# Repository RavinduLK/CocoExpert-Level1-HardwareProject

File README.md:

# CocoExpert-Level1-HardwareProject
CocoExpert is an automated coconut breaking, scraping, and grinding machine with a focus on ensuring safety for housewives and frequent users, thereby eliminating the need for manual intervention

# Machine Animation Video
https://drive.google.com/drive/u/0/folders/18UEq-plaGjheWkudtf2PqrmO_yfCV39f

# Final Schematic Diagram

# Block Diagram

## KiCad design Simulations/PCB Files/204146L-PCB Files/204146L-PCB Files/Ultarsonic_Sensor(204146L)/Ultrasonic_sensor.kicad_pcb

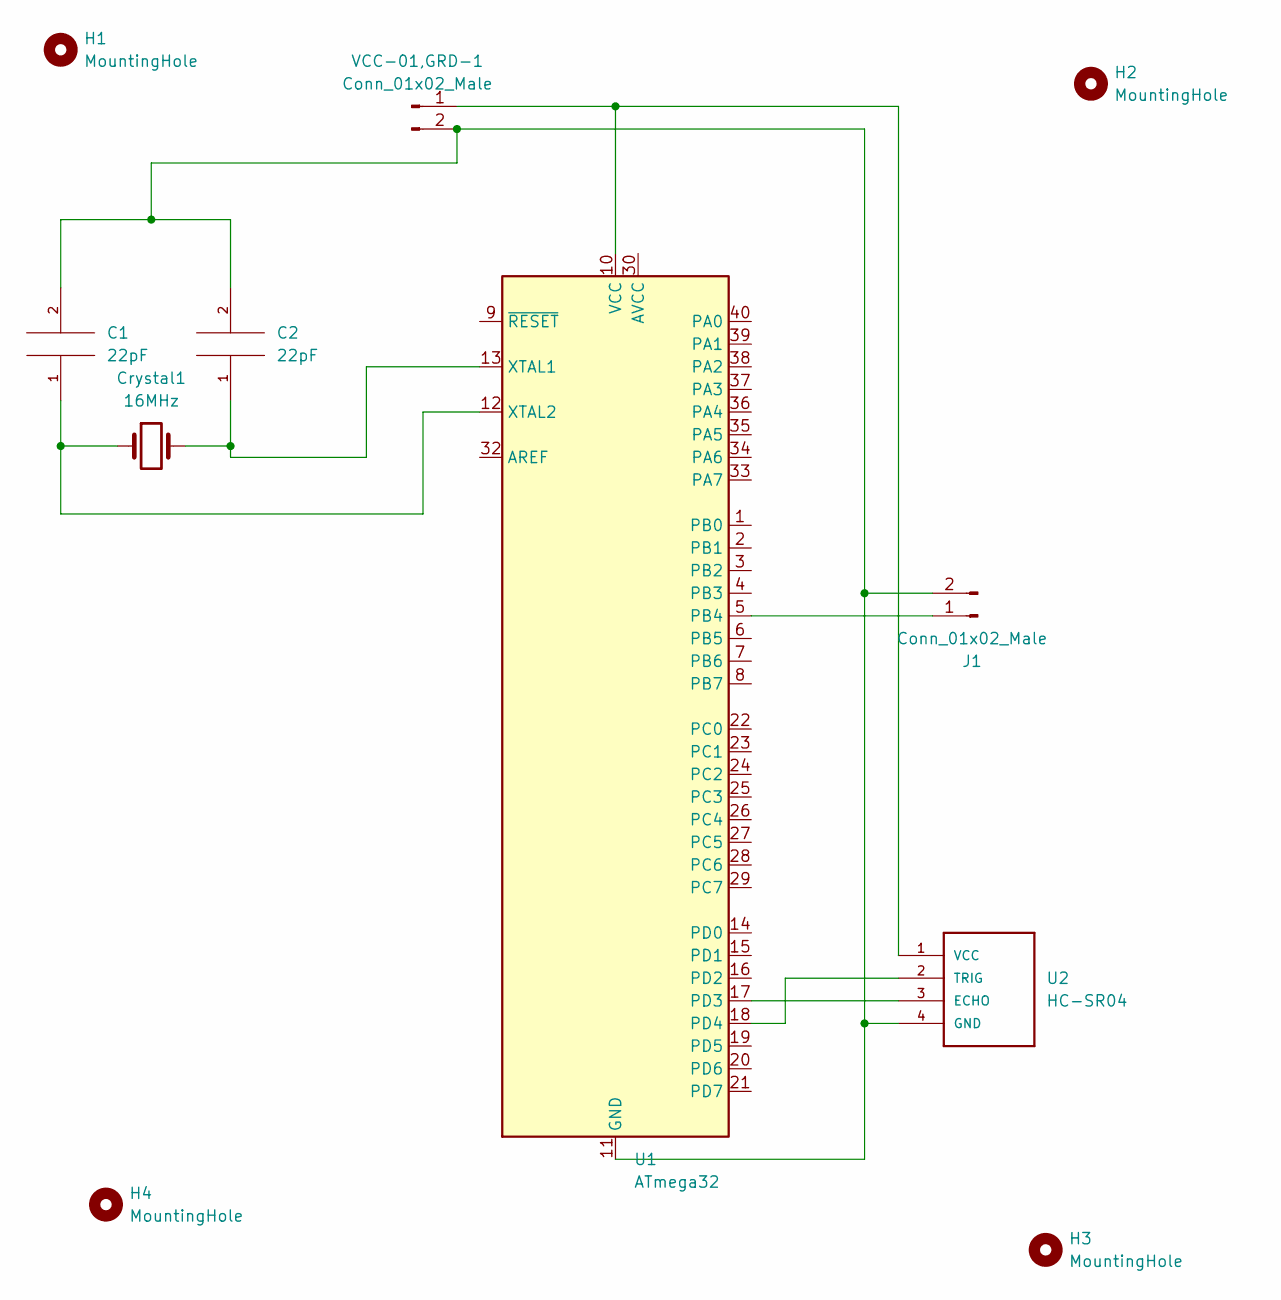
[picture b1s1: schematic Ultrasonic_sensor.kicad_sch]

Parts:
C1, C2: 22pF; CP_Axial_L10.0mm_D4.5mm_P15.00mm_Horizontal
Crystal1: 16MHz; Crystal_AT310_D3.0mm_L10.0mm_Horizontal
H1, H2, H3, H4: MountingHole; MountingHole_2.5mm
J1: Conn_01x02_Male; PinHeader_1x02_P1.00mm_Horizontal
U1: ATmega32; DIP-40_W15.24mm
U2: HC-SR04; PinHeader_1x04_P2.54mm_Horizontal
VCC-01,GRD-1: Conn_01x02_Male; PinHeader_1x02_P2.00mm_Horizontal

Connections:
unnamed: C1.1, Crystal1.1, U1.12 (XTAL2)
unnamed 1: C1.2, C2.2, J1.2, U1.11 (GND), U1.31 (GND), U2.4 (GND), VCC-01,GRD-1.2; also elsewhere on the board
unnamed: C2.1, Crystal1.2, U1.13 (XTAL1)
unnamed: J1.1, U1.5 (PB4)
unnamed 4: U1.10 (VCC), U2.1 (VCC), VCC-01,GRD-1.1; also elsewhere on the board
unnamed: U1.17 (PD3), U2.3 (ECHO)
unnamed: U1.18 (PD4), U2.2 (TRIG)

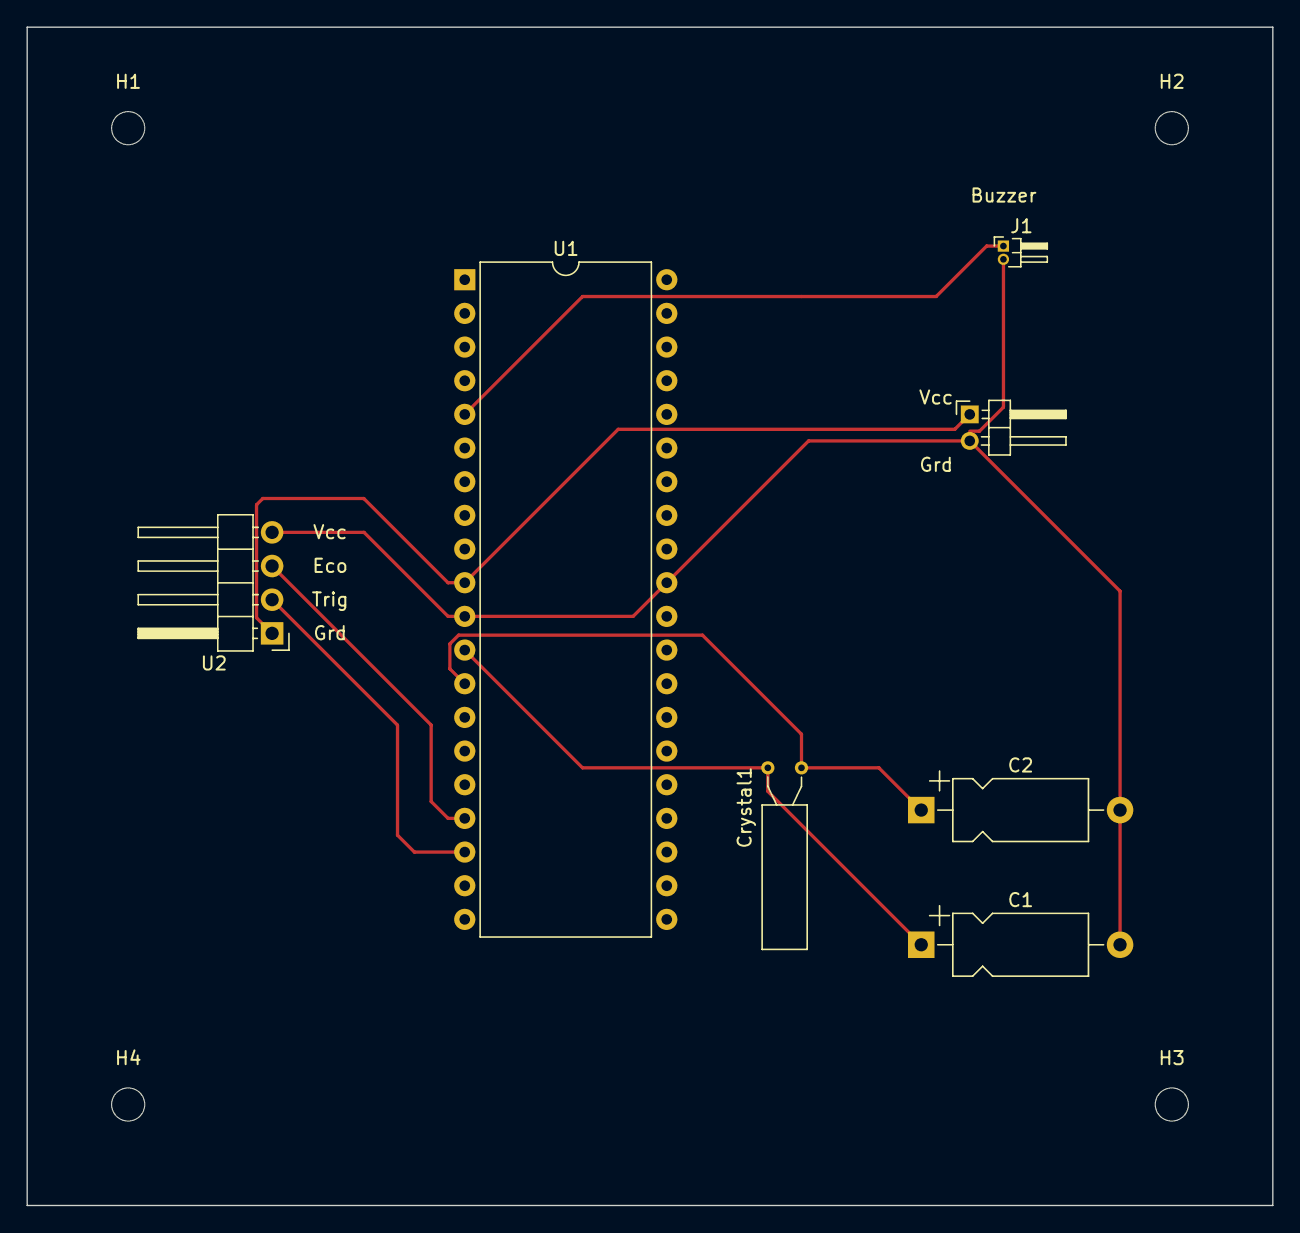
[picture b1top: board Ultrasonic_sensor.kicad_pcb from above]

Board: 2 copper layers, 94.0 x 88.9 mm, 11 parts (0 on the bottom side), 7 nets.

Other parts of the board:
Vcc,Grd: Conn_01x02_Male; PinHeader_1x02_P2.00mm_Horizontal

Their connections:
unnamed 1: Vcc,Grd.2; also elsewhere on the board
unnamed 4: Vcc,Grd.1; also elsewhere on the board

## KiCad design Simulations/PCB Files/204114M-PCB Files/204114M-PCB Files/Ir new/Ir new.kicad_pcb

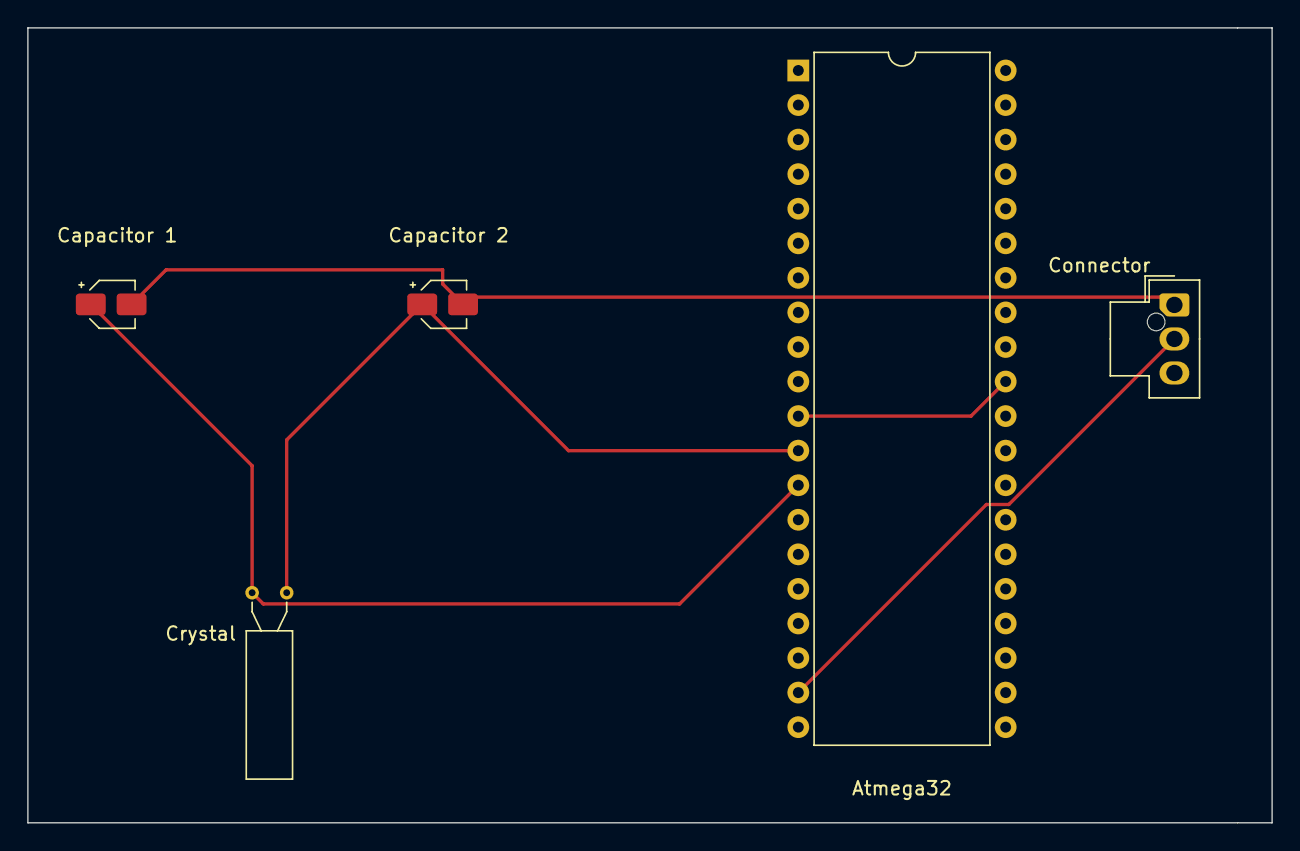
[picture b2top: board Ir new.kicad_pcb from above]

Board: 2 copper layers, 91.4 x 58.4 mm, 5 parts (0 on the bottom side), 5 nets.

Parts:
Atmega32: ATmega32-16P; DIP-40_W15.24mm
Capacitor 1, Capacitor 2: CAP; CP_Elec_3x5.4
Connector: Conn_01x03_Female; Molex_Nano-Fit_105309-xx03_1x03_P2.50mm_Vertical
Crystal: Crystal; Crystal_AT310_D3.0mm_L10.0mm_Horizontal

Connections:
GND: Capacitor 1.2, Capacitor 2.2, Connector.1
unnamed: Atmega32.13 (XTAL1), Capacitor 1.1, Crystal.1
unnamed: Atmega32.12 (XTAL2), Capacitor 2.1, Crystal.2
unnamed: Atmega32.19 (PD5), Connector.2
unnamed: Atmega32.11 (GND), Atmega32.31 (GND)

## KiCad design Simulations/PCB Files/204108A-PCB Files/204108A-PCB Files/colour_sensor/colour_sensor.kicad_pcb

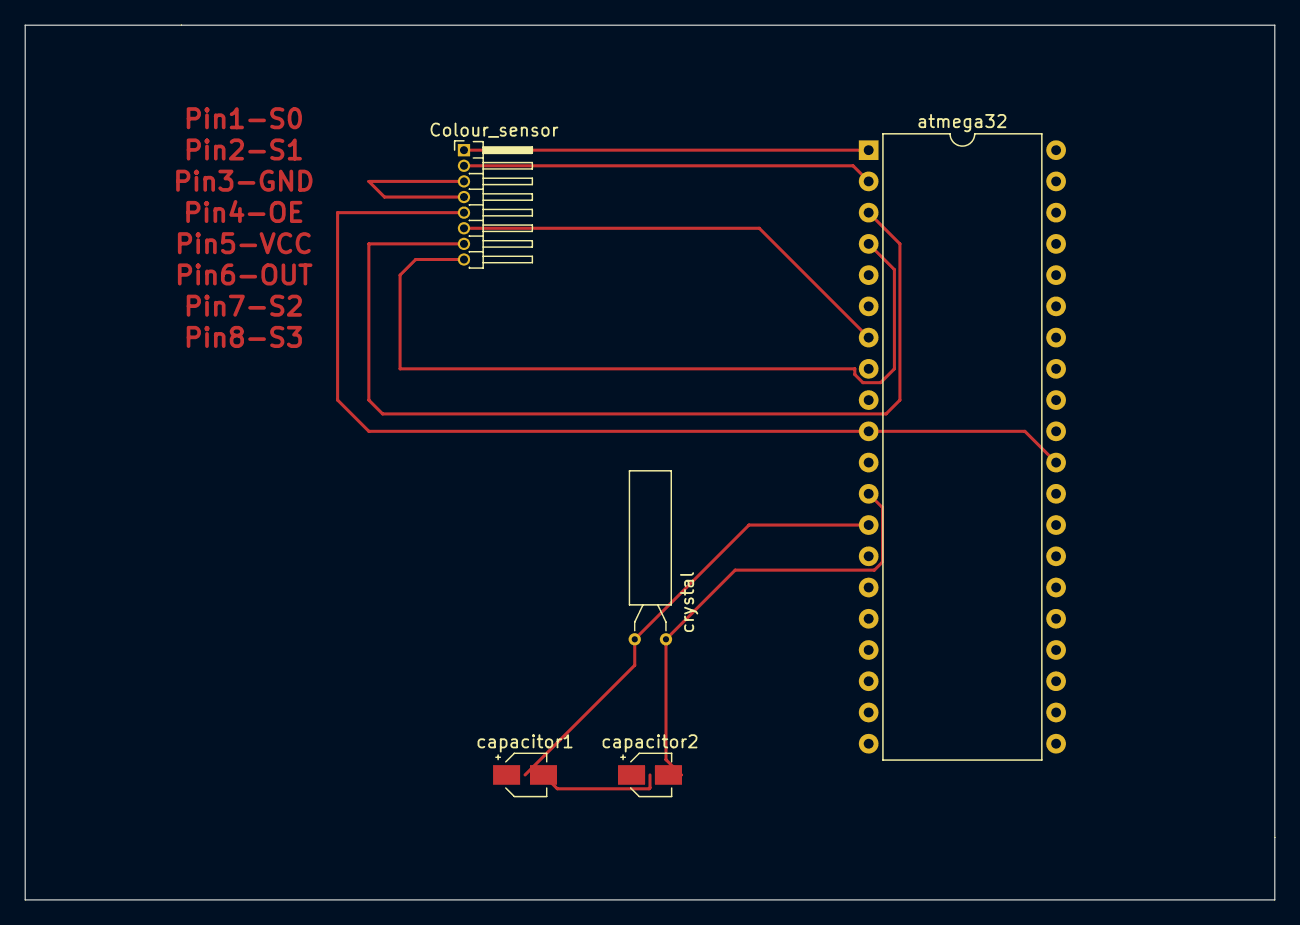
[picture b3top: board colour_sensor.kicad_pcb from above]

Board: 2 copper layers, 101.6 x 71.1 mm, 5 parts (0 on the bottom side), 11 nets.

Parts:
Colour_sensor: TCS3200D-TR; PinHeader_1x08_P1.27mm_Horizontal
atmega32: ATmega32-16P; DIP-40_W15.24mm
capacitor1, capacitor2: C_Polarized_US; CP_Elec_3x5.3
crystal: Crystal; Crystal_AT310_D3.0mm_L10.0mm_Horizontal

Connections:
+5V: Colour_sensor.VCC (VDD), atmega32.10 (VCC), atmega32.30 (AVCC)
Earth: Colour_sensor.GND (~OE), Colour_sensor.OE (GND)
GND: capacitor1.1, capacitor2.1
unnamed: atmega32.12 (XTAL2), capacitor2.2, crystal.1
unnamed: atmega32.13 (XTAL1), capacitor1.2, crystal.2
unnamed: Colour_sensor.S0, atmega32.1 (PB0)
unnamed: Colour_sensor.S1, atmega32.2 (PB1)
unnamed: Colour_sensor.OUT, atmega32.7 (PB6)
unnamed: Colour_sensor.S2, atmega32.3 (PB2)
unnamed: Colour_sensor.S3, atmega32.4 (PB3)
unnamed: atmega32.11 (GND), atmega32.31 (GND)

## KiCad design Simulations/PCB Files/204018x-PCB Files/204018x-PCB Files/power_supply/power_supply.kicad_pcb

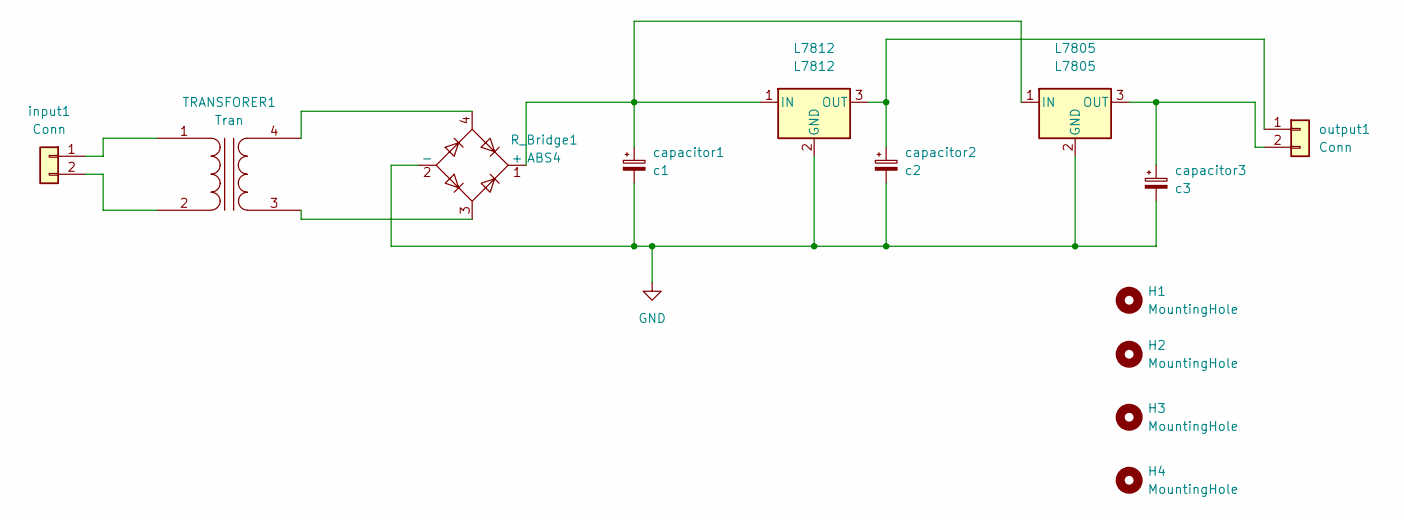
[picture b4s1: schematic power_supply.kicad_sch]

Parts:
H1: MountingHole; MountingHole_2.1mm
H2, H3, H4: MountingHole
L7805: L7805; TO-220-3_Horizontal_TabDown
L7812: L7812; TO-220-3_Horizontal_TabDown
R_Bridge1: ABS4; Diode_Bridge_Diotec_ABS
TRANSFORER1: Tran; PinHeader_1x04_P2.54mm_Vertical
capacitor1: c1; CP_Elec_3x5.4
capacitor2: c2; CP_Elec_4x3
capacitor3: c3; CP_Elec_4x3
input1: Conn; PinSocket_1x02_P1.00mm_Vertical
output1: Conn; PinSocket_1x02_P1.00mm_Vertical

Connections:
GND: L7805.2 (GND), L7812.2 (GND), R_Bridge1.2 (-), capacitor1.2, capacitor2.2, capacitor3.2
unnamed: L7805.1 (IN), L7812.1 (IN), R_Bridge1.1 (+), capacitor1.1
unnamed: L7805.3 (OUT), capacitor3.1, output1.2
unnamed: L7812.3 (OUT), capacitor2.1, output1.1
unnamed: R_Bridge1.3, TRANSFORER1.3 (SA)
unnamed: R_Bridge1.4, TRANSFORER1.4 (SB)
unnamed: TRANSFORER1.1 (AA), input1.1
unnamed: TRANSFORER1.2 (AB), input1.2

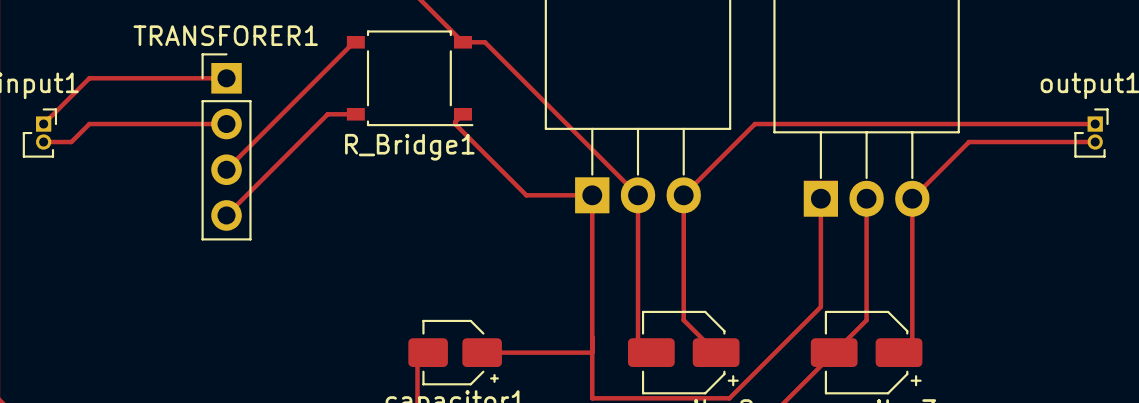
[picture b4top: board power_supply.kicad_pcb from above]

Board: 2 copper layers, 13 parts (0 on the bottom side), 8 nets.

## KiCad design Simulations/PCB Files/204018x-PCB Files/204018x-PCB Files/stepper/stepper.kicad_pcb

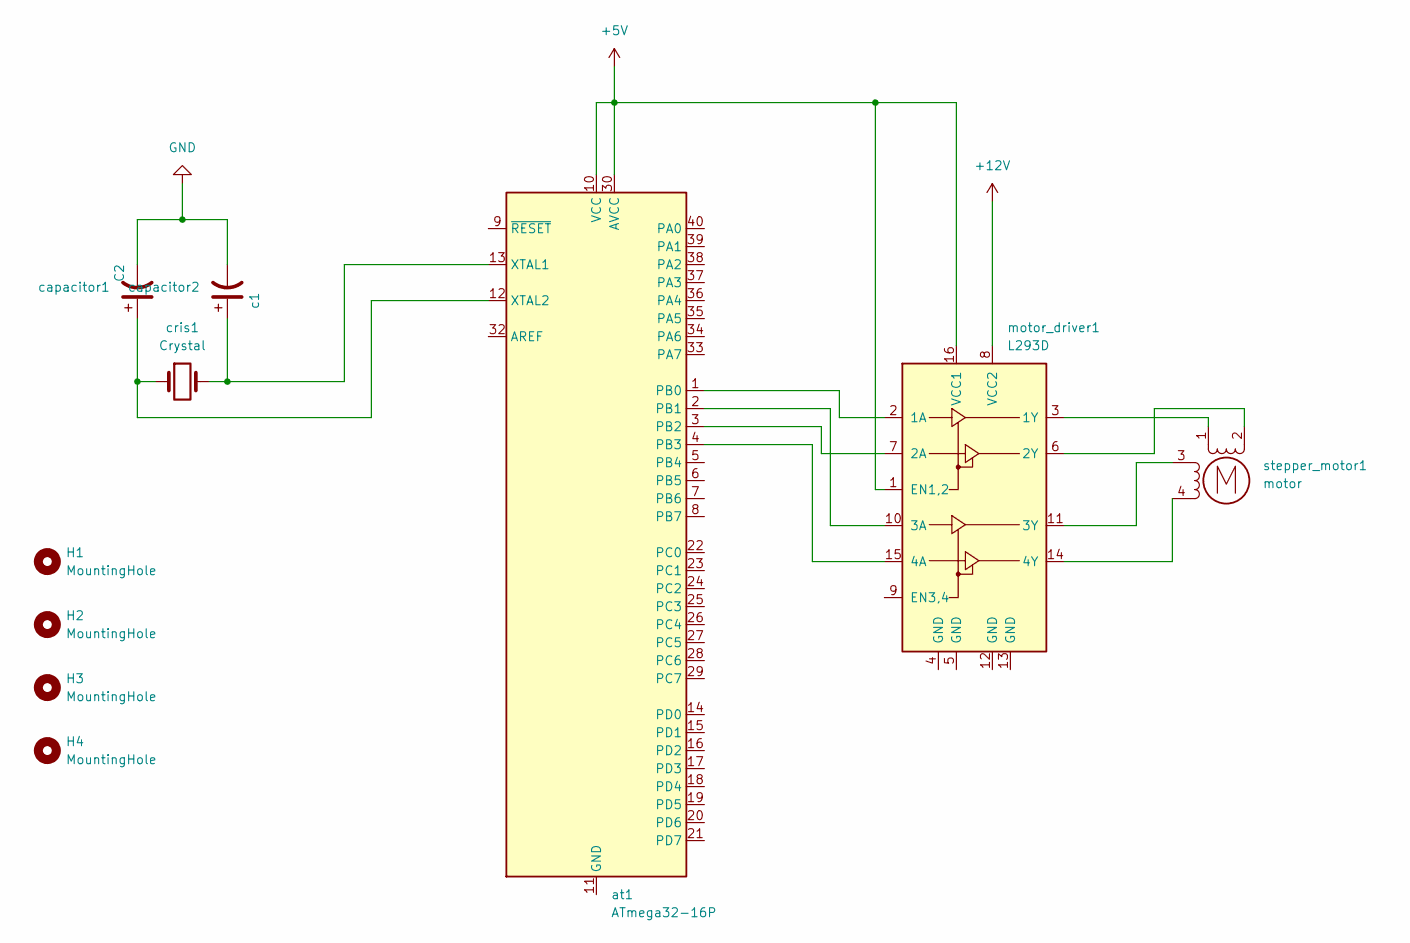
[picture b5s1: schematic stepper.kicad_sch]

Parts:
H1, H2, H3, H4: MountingHole; MountingHole_2.1mm
at1: ATmega32-16P; DIP-40_W15.24mm
capacitor1: C2; CP_Elec_3x5.3
capacitor2: c1; CP_Elec_3x5.3
cris1: Crystal; Crystal_AT310_D3.0mm_L10.0mm_Horizontal
motor_driver1: L293D; DIP-16_W7.62mm
stepper_motor1: motor; PinHeader_1x04_P1.27mm_Horizontal

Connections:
+5V: at1.10 (VCC), at1.30 (AVCC), motor_driver1.1 (EN1,2), motor_driver1.16 (VCC1)
+12V: motor_driver1.8 (VCC2)
GND: capacitor1.2, capacitor2.2
unnamed: at1.1 (PB0), motor_driver1.2 (1A)
unnamed: at1.2 (PB1), motor_driver1.10 (3A)
unnamed: at1.3 (PB2), motor_driver1.7 (2A)
unnamed: at1.4 (PB3), motor_driver1.15 (4A)
unnamed: at1.11 (GND), at1.31 (GND)
unnamed: at1.12 (XTAL2), capacitor1.1, cris1.1
unnamed: at1.13 (XTAL1), capacitor2.1, cris1.2
unnamed: motor_driver1.3 (1Y), stepper_motor1.1
unnamed: motor_driver1.6 (2Y), stepper_motor1.2 (-)
unnamed: motor_driver1.11 (3Y), stepper_motor1.3
unnamed: motor_driver1.14 (4Y), stepper_motor1.4

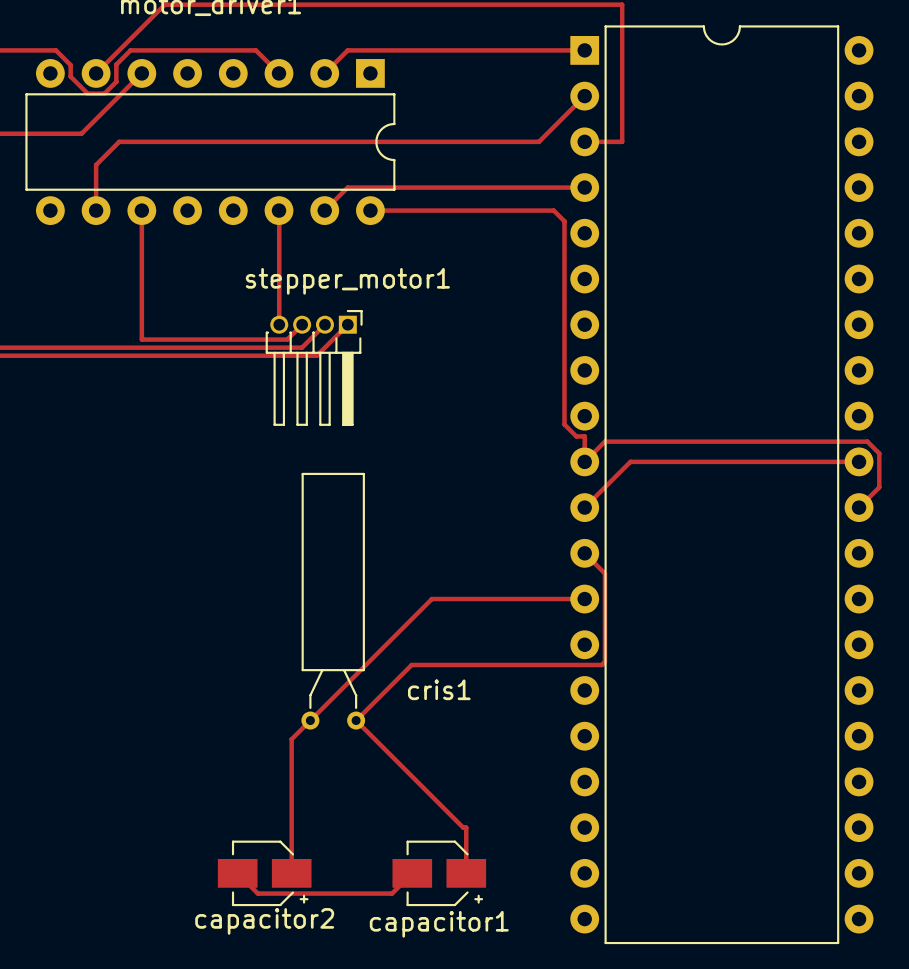
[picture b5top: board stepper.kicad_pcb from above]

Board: 2 copper layers, 10 parts (0 on the bottom side), 13 nets.

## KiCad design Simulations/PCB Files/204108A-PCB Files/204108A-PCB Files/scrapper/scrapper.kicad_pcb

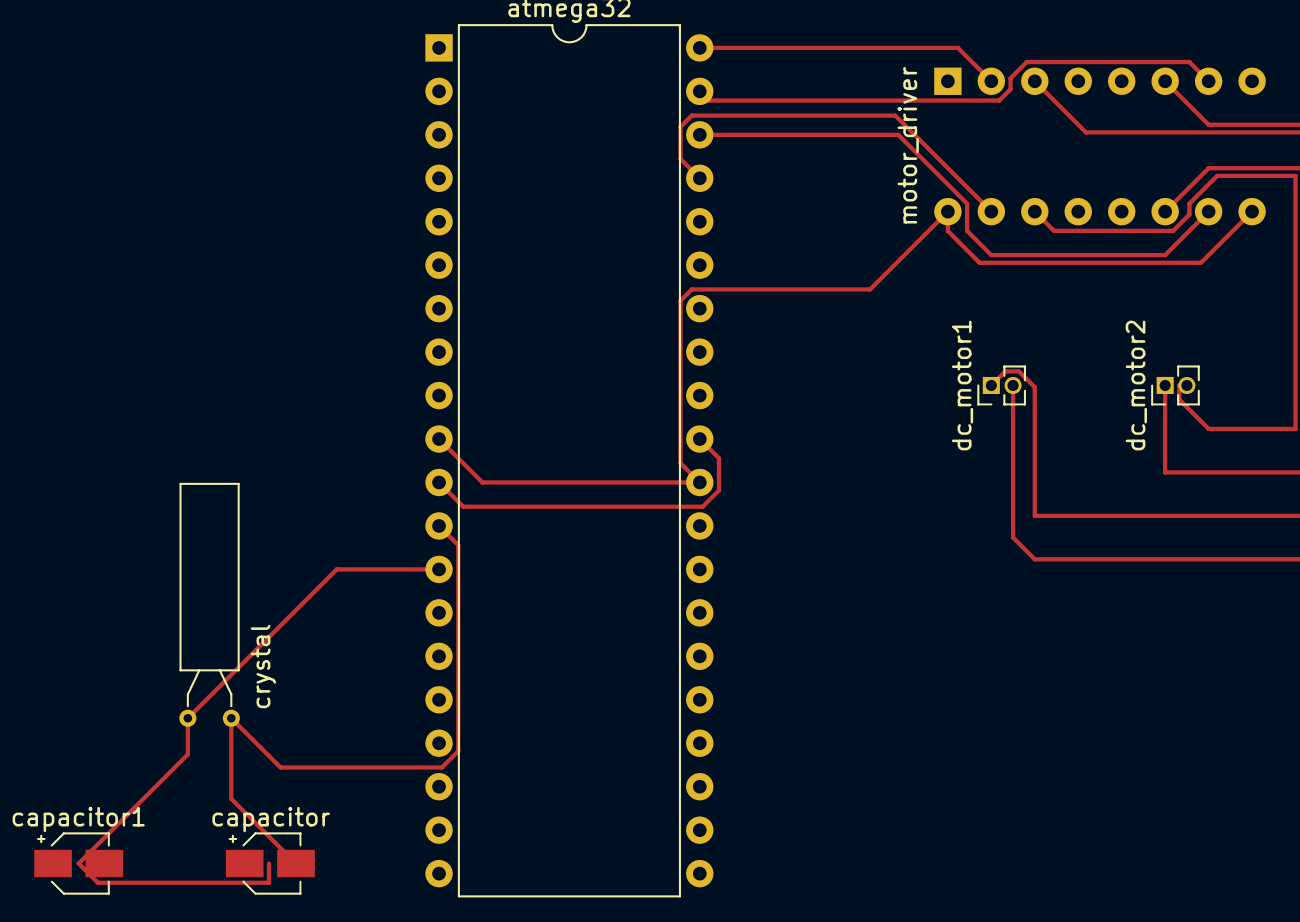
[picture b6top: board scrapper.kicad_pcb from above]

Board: 2 copper layers, 7 parts (1 on the bottom side), 13 nets.

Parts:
atmega32: ATmega32-16P; DIP-40_W15.24mm
capacitor, capacitor1: C_Polarized_US; CP_Elec_3x5.3
crystal: Crystal; Crystal_AT310_D3.0mm_L10.0mm_Horizontal
dc_motor1, dc_motor2: Motor_DC; PinHeader_1x02_P1.27mm_Vertical
motor_driver: L293D; DIP-16_W7.62mm

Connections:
+5V: atmega32.10 (VCC), atmega32.30 (AVCC), motor_driver.1 (EN1,2), motor_driver.9 (EN3,4), motor_driver.16 (VCC1)
GND: capacitor.1, capacitor1.1
unnamed: atmega32.12 (XTAL2), capacitor.2, crystal.1
unnamed: atmega32.13 (XTAL1), capacitor1.2, crystal.2
unnamed: dc_motor1.1 (+), motor_driver.3 (1Y)
unnamed: dc_motor1.2 (-), motor_driver.6 (2Y)
unnamed: dc_motor2.1 (+), motor_driver.11 (3Y)
unnamed: dc_motor2.2 (-), motor_driver.14 (4Y)
unnamed: atmega32.11 (GND), atmega32.31 (GND)
unnamed: atmega32.37 (PA3), motor_driver.15 (4A)
unnamed: atmega32.38 (PA2), motor_driver.10 (3A)
unnamed: atmega32.39 (PA1), motor_driver.7 (2A)
unnamed: atmega32.40 (PA0), motor_driver.2 (1A)

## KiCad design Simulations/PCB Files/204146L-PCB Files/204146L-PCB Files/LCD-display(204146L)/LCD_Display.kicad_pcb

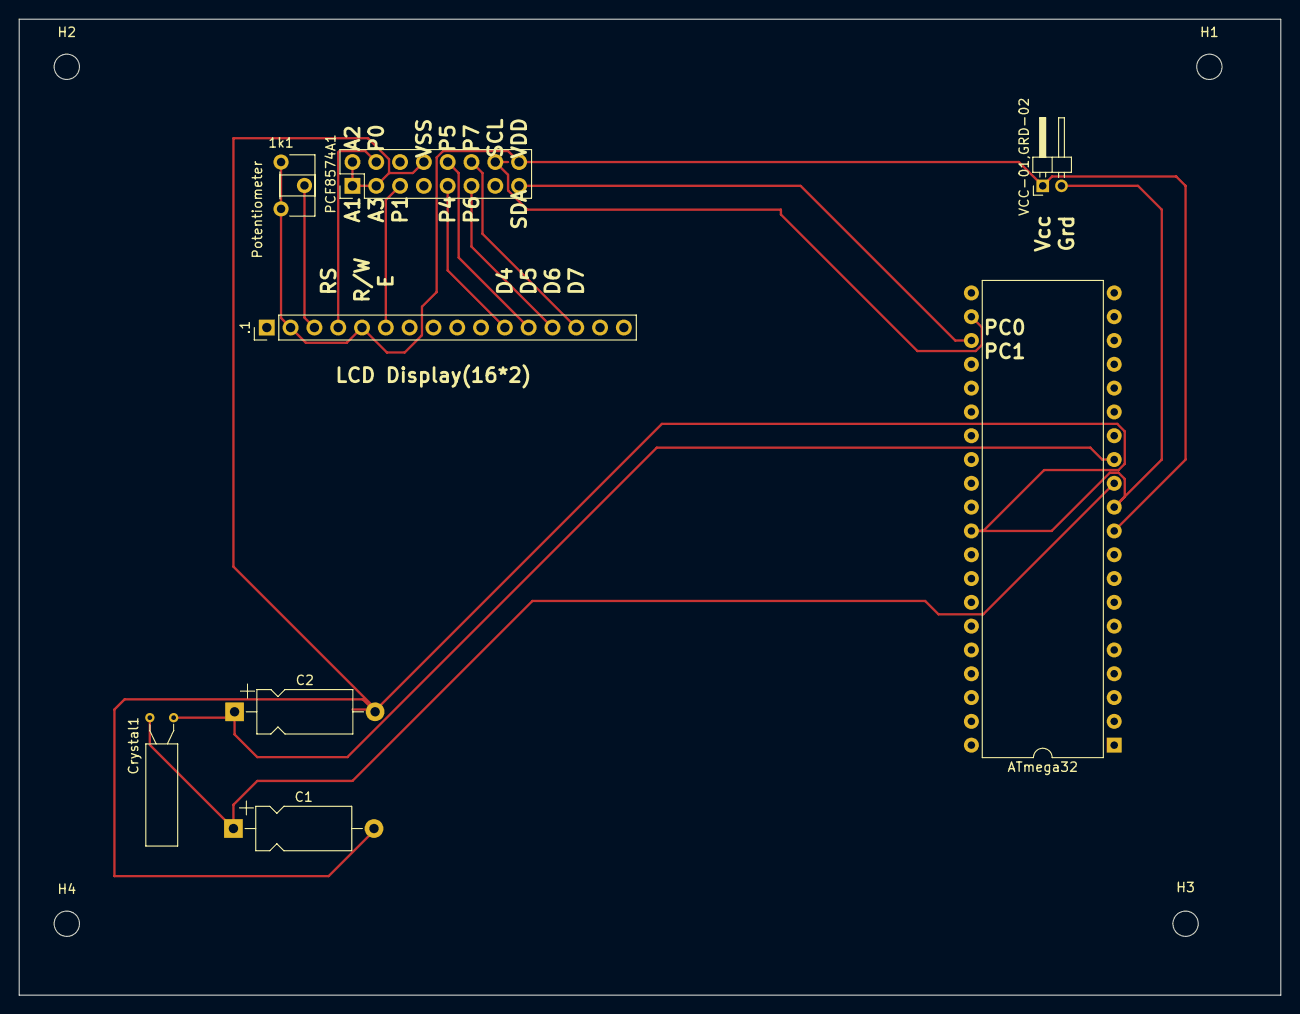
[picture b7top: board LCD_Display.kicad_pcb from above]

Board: 2 copper layers, 134.6 x 104.1 mm, 12 parts (0 on the bottom side), 5 nets.

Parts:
1k1: Potentiometer; Potentiometer_ACP_CA6-H2,5_Horizontal
.1: 16*2 LCD; PinHeader_1x16_P2.54mm_Vertical
ATmega32: ATmega32; DIP-40_W15.24mm
C1, C2: 22pF; CP_Axial_L10.0mm_D4.5mm_P15.00mm_Horizontal
Crystal1: 16MHz; Crystal_AT310_D3.0mm_L10.0mm_Horizontal
H1, H2, H3, H4: MountingHole; MountingHole_2.7mm
PCF8574A1: .; PinHeader_2x08_P2.54mm_Vertical
VCC-01,GRD-02: Conn_01x02_Male; PinHeader_1x02_P2.00mm_Horizontal

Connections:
unnamed: 1k1.1, 1k1.3, .1.2 (VDD), .1.5 (R/W), ATmega32.PIN 10 (VCC), PCF8574A1.16 (VDD), VCC-01,GRD-02.1
unnamed: ATmega32.12 (XTAL2), C1.1, Crystal1.1
unnamed: ATmega32.11 (GND), ATmega32.31 (GND), C1.2, C2.2, PCF8574A1.1 (A0), PCF8574A1.2 (A1), PCF8574A1.3 (A2), PCF8574A1.8 (VSS), VCC-01,GRD-02.2
unnamed: ATmega32.13 (XTAL1), C2.1, Crystal1.2
unnamed: ATmega32.23 (PC1), PCF8574A1.15 (SDA)

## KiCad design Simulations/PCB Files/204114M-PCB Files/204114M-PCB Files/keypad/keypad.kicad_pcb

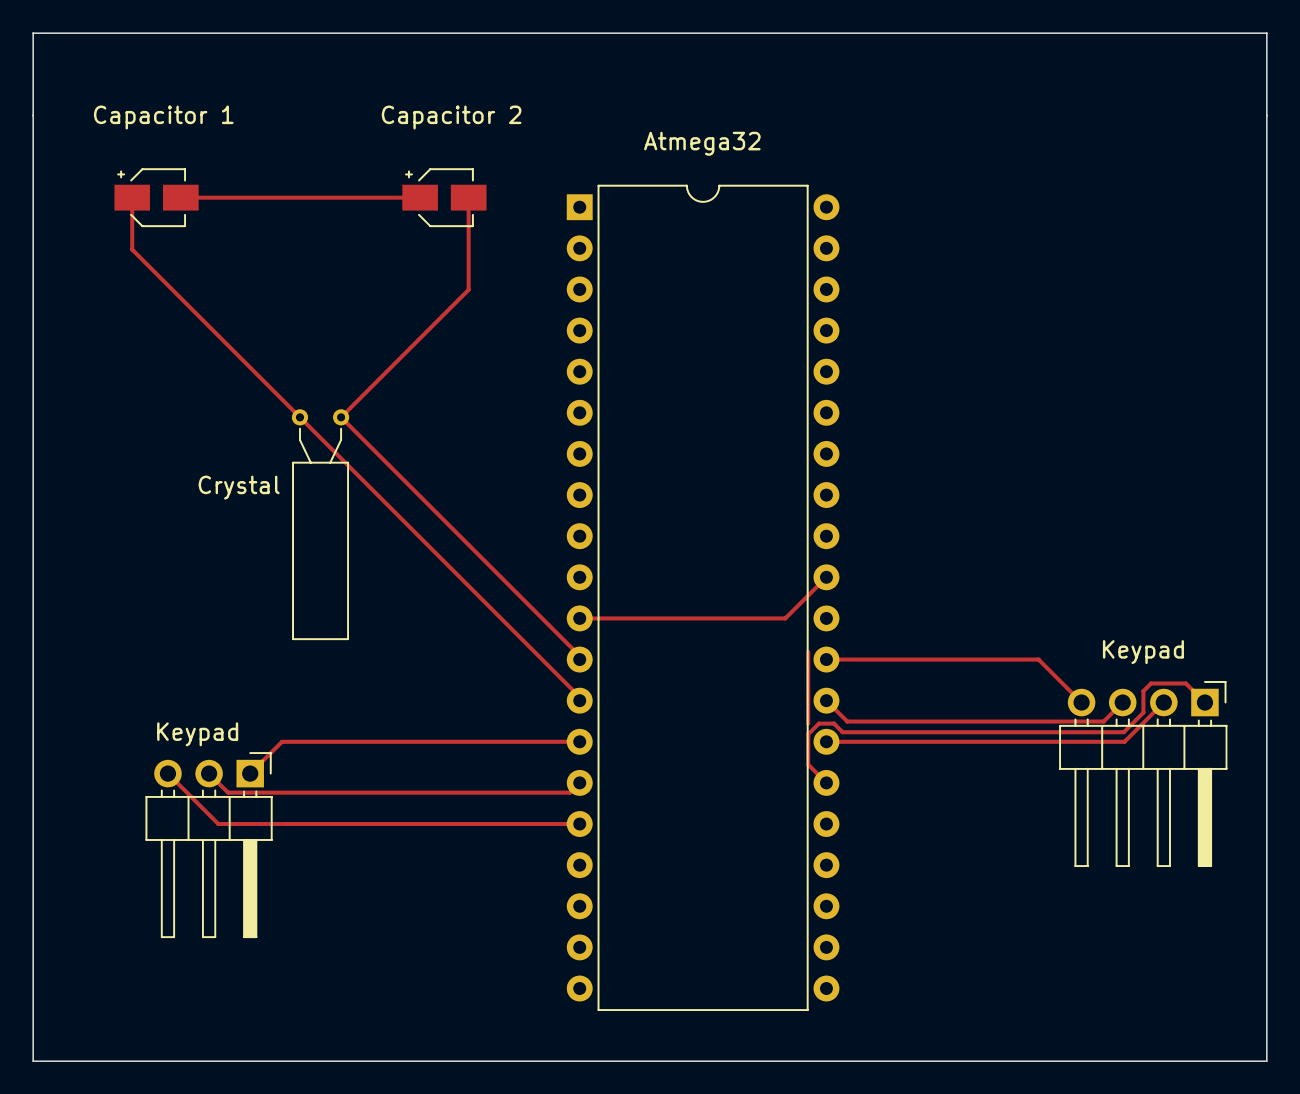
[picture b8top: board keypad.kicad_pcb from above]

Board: 2 copper layers, 76.2 x 63.5 mm, 6 parts (0 on the bottom side), 11 nets.

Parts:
Atmega32: ATmega32-16P; DIP-40_W15.24mm
Capacitor 1, Capacitor 2: 22pF; CP_Elec_3x5.3
Crystal: Crystal; Crystal_AT310_D3.0mm_L10.0mm_Horizontal
Keypad: Conn_01x03_Male; PinHeader_1x03_P2.54mm_Horizontal
Keypad#2: Conn_01x04_Male; PinHeader_1x04_P2.54mm_Horizontal

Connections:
GND: Capacitor 1.2, Capacitor 2.1
unnamed: Atmega32.13 (XTAL1), Capacitor 1.1, Crystal.1
unnamed: Atmega32.12 (XTAL2), Capacitor 2.2, Crystal.2
unnamed: Atmega32.11 (GND), Atmega32.31 (GND)
unnamed: Atmega32.14 (PD0), Keypad.1
unnamed: Atmega32.15 (PD1), Keypad.2
unnamed: Atmega32.16 (PD2), Keypad.3
unnamed: Atmega32.26 (PC4), Keypad#2.1
unnamed: Atmega32.27 (PC5), Keypad#2.2
unnamed: Atmega32.28 (PC6), Keypad#2.3
unnamed: Atmega32.29 (PC7), Keypad#2.4

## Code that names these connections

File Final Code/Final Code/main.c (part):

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	i2c_write(0x70);
	lcd_init();
	unsigned char x;
	// make PA0 to PA3 = output and PA4 to PA7 = Input
	DDRC |=0X0f; //DC MOTOR CUTDISK
	DDRC |= 0XF0; //making keypad row pin as output
	DDRB = 0XFF;//making stepper pin output
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							_delay_ms(500);
							DC3time();//grind
							
							//PORTB = PORTB | 1 << PB4;//buzzer will on
							lcd_cmd(0x01);
							HCSR04();
							_delay_ms(1000);
						}
						else if(x=='2')
						{
							//PORTB = PORTB | 1 << PB4;//buzzer will on
							lcd_cmd(0x01);
							HCSR04();
							_delay_ms(1000);
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							DC3time();//grind
							_delay_ms(300);
							
							//PORTB = PORTB | 1 << PB4;//buzzer will on
							lcd_cmd(0x01);
							HCSR04();
							_delay_ms(1000);
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						}
						if(x=='2')
						{
							//PORTB = PORTB | 1 << PB4;//buzzer will on
							HCSR04();
							_delay_ms(1000);
							//machine off
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			}
			else if(x=='2')
			{
				//PORTB = PORTB | 1 << PB4;//buzzer will on
				HCSR04();
				/*_delay_ms(1000);
				lcd_cmd(0x01);
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	
	DDRB = DDRB | 1 << DDB4; // Set LED pin as an output. Change this according to your circuit
	DDRD = DDRD | 1 << DDD4; // Set Trigger pin as an output. Change this according to your circuit
	DDRD = DDRD & ~(1 << DDD3); // Set Echo pin(INT0 - PD2 on atmega32) as an input.
	PORTD = PORTD & ~(1 << PD3); //Disable pull-up resistor for echo pin. Read from page number 49
	_delay_ms(50);

	GICR |= 1<<INT1; //Enable interrupt for INT0 (Page number 67), For other pins change 0 to 1 or 2. See UltrasonicHCSR04v1.pdf
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	while(1){
		
		//Send a 15us pulse to the trigger pin
		PORTD = PORTD | 1<<PD4;
		_delay_us(15);
		PORTD = PORTD & ~(1<<PD4);
		_delay_us(15);
		//Then echo pin will go hight. That interrupt will cause function ISR(INT0_vect) to get executed for the first time.
		//After detecting reflected sound wave, echo pin will go low. That interrupt will cause function ISR(INT0_vect) to get executed for the second time.
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		//Turn on or off the LED based on the condition
		if (distance < 15)
		{
			PORTB = PORTB | 1 << PB4;
			
			lcd_cmd(0x01);
			lcd_msg("Check coco water");
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		else
		{
			_delay_ms(1200);
			PORTB = PORTB & ~ (1 << PB4);
			lcd_cmd(0x01);
			lcd_msg("---THANK YOU---");
			//_delay_ms(1200);
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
